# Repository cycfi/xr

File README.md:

# xr
XR Extended Response Pickups

The Cycfi XR Extended Response Pickups utilize low-impedance coils (Lo-Z 350Ω to 500Ω DCR) which 
inherently have full frequency response from 20Hz to 20kHz and beyond. Unlike traditional high-
impedance passive pickups there are no big peaks and dips in the spectrum, typically perceived as 
the pickup’s “character”. That does not mean that Lo-Z pickups lack character. In fact a Lo-Z coil’s 
characteristically wide bandwidth gives it a voice all its own. The pickups are very rich in harmonics, 
with uber-clean sounds, lots of overtones and crystal clear highs. They have a lot more harmonic 
content than even the bright Stratocaster pickup (which has frequency response that rolls off at 
around 5KHz.) On the low end of the audio spectrum you get tight, well-defined and focused bass 
all the way down to 20Hz.

This work is licensed under a [Creative Commons Attribution-NonCommercial 4.0 
International License](http://creativecommons.org/licenses/by-nc/4.0/).

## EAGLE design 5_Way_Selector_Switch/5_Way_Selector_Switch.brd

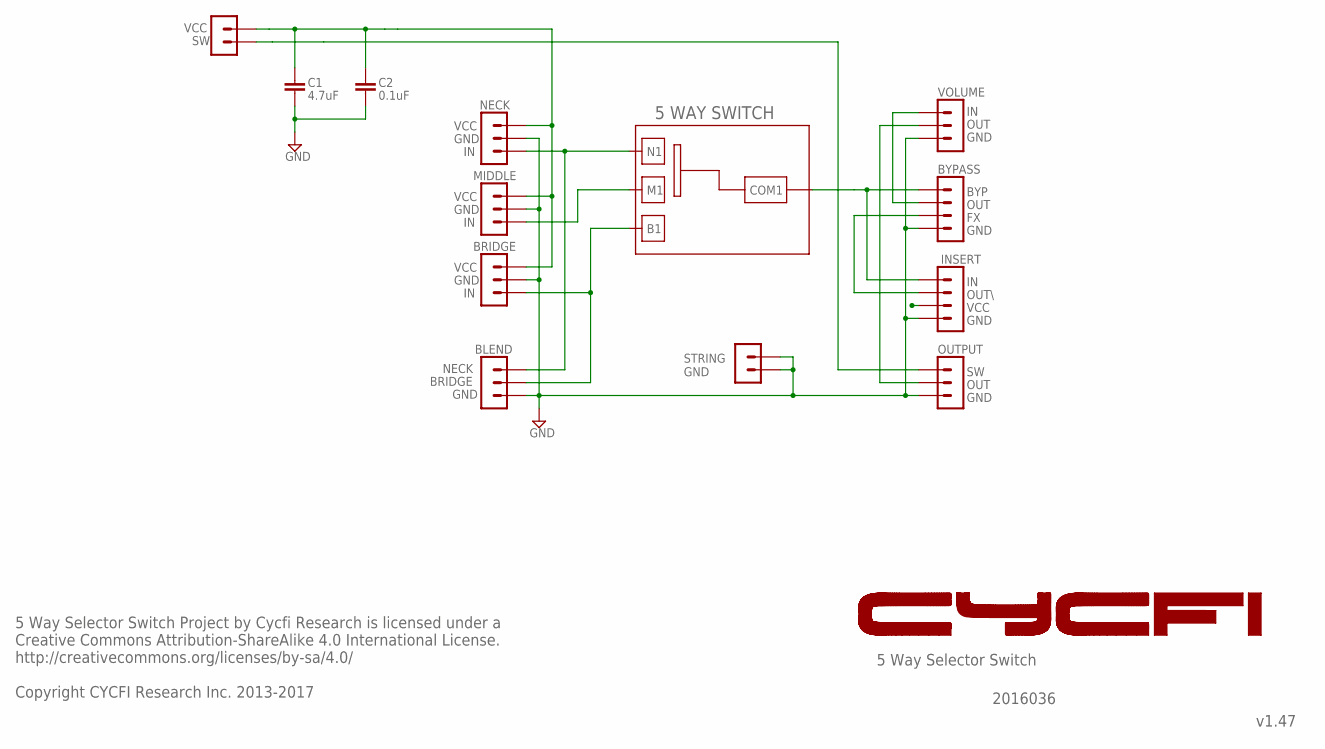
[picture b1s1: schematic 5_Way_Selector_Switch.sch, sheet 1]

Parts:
C1: 4.7uF; C0603
C2: 0.1uF; C0603
H3: 2PIN-SMD-2.54MM; 2P-SMD-2.54MM
U$3: 5WAY_SW_1; 5WAY_SW_CASTELLATED

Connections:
5WOUT: U$3.COM1; also elsewhere on the board
9V: C1.1, C2.1; also elsewhere on the board
B1: U$3.B1; also elsewhere on the board
GND: C1.2, C2.2, H3.P$1 (1), H3.P$2 (2); also elsewhere on the board
M1: U$3.M1; also elsewhere on the board
N1: U$3.N1; also elsewhere on the board

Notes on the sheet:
STRING GND
VCC
GND
NECK
BRIDGE
BLEND
BYP
OUT
OUT\
VOLUME
INSERT
OUTPUT
BYPASS
5 Way Selector Switch
v1.47
5 Way Selector Switch Project by Cycfi Research is licensed under a Creative Commons Attribution-ShareAlike 4.0 International License. http://creativecommons.org/licenses/by-sa/4.0/ Copyright CYCFI Research Inc. 2013-2017
2016036
MIDDLE

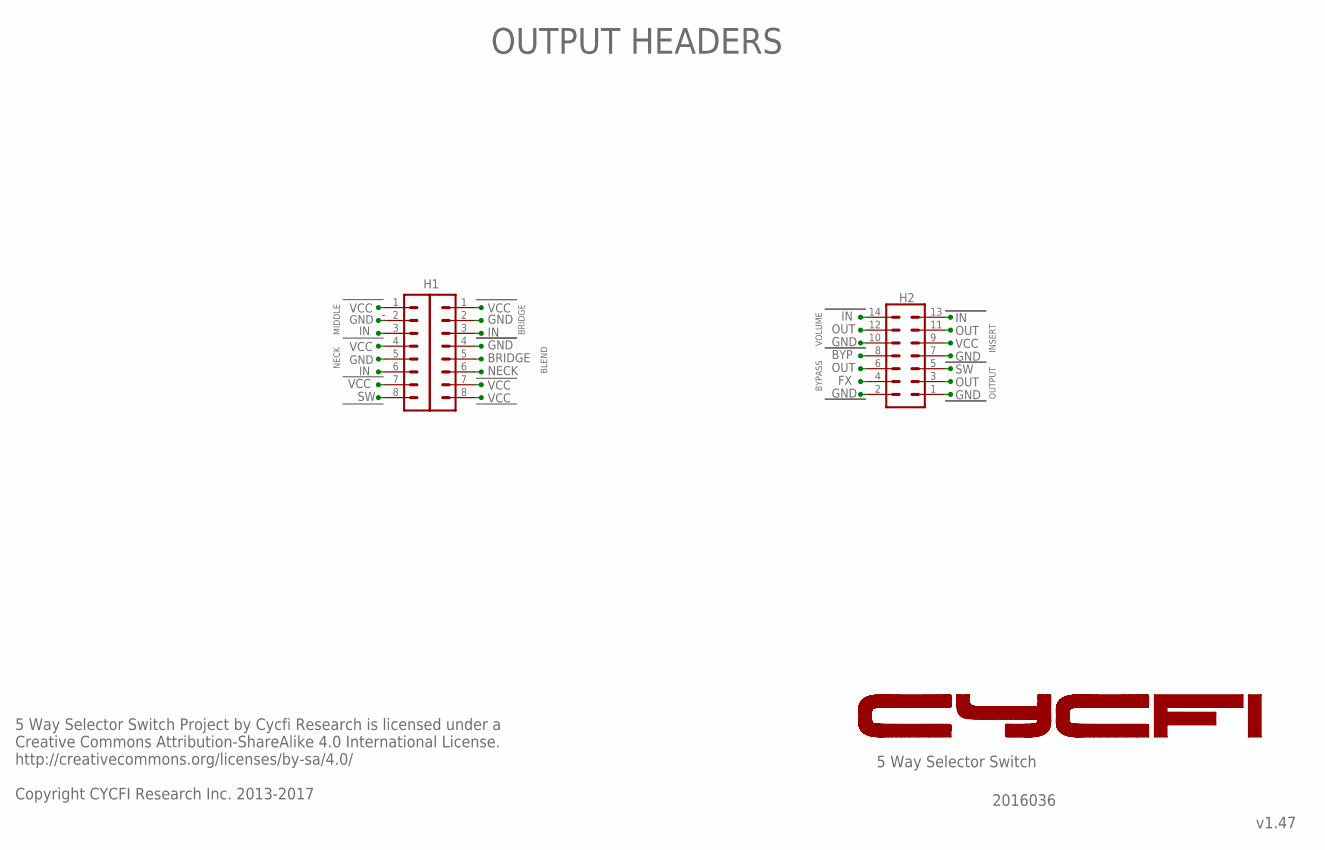
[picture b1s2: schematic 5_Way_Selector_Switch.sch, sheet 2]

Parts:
H2: MA07-2
SV1, SV2: MA08-1_

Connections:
5WOUT: H2.8, H2.13; also elsewhere on the board
9V: H2.9, SV1.1, SV1.7, SV1.8, SV2.1, SV2.4, SV2.7; also elsewhere on the board
B1: SV1.3, SV1.5; also elsewhere on the board
FX: H2.4, H2.11
GND: H2.1, H2.2, H2.7, H2.10, SV1.2, SV1.4, SV2.2, SV2.5; also elsewhere on the board
IN_VOL/MAIN_OUT: H2.6, H2.14
M1: SV2.3; also elsewhere on the board
N1: SV1.6, SV2.6; also elsewhere on the board
OUT(VOL): H2.3, H2.12
SW: H2.5, SV2.8

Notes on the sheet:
BYP
OUT
GND
VCC
NECK
BRIDGE
VOLUME
BYPASS
INSERT
OUTPUT
5 Way Selector Switch
v1.47
5 Way Selector Switch Project by Cycfi Research is licensed under a Creative Commons Attribution-ShareAlike 4.0 International License. http://creativecommons.org/licenses/by-sa/4.0/ Copyright CYCFI Research Inc. 2013-2017
2016036
OUTPUT HEADERS
BLEND
MIDDLE

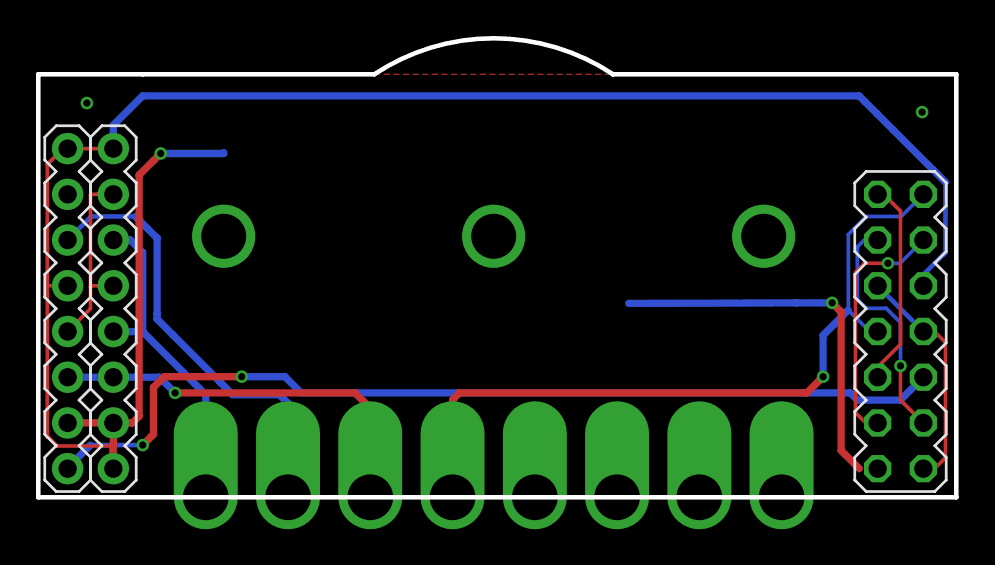
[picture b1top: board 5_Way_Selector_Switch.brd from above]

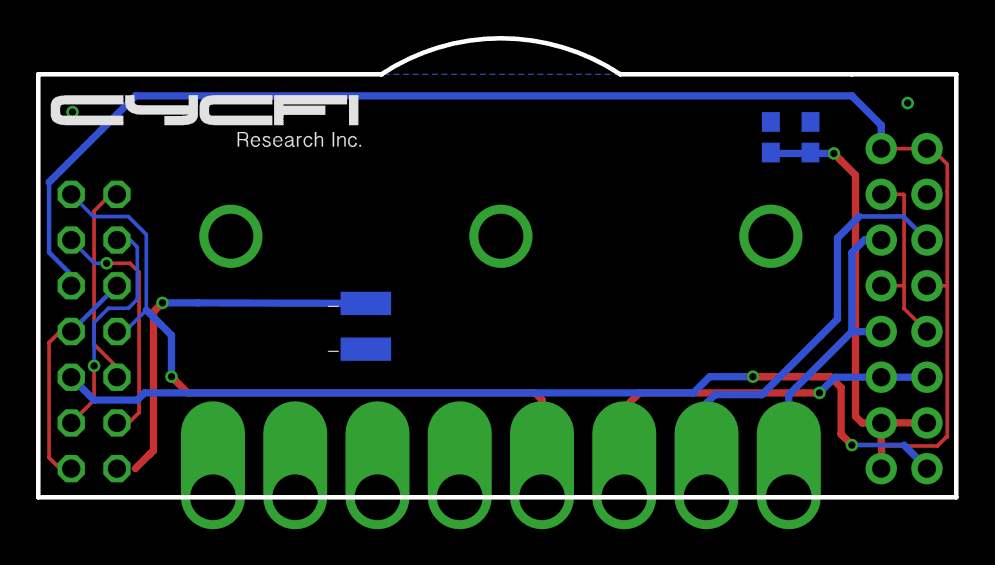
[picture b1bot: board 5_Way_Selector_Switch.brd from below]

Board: 2 copper layers, 51.0 x 25.5 mm, 7 parts (3 on the bottom side), 10 nets.

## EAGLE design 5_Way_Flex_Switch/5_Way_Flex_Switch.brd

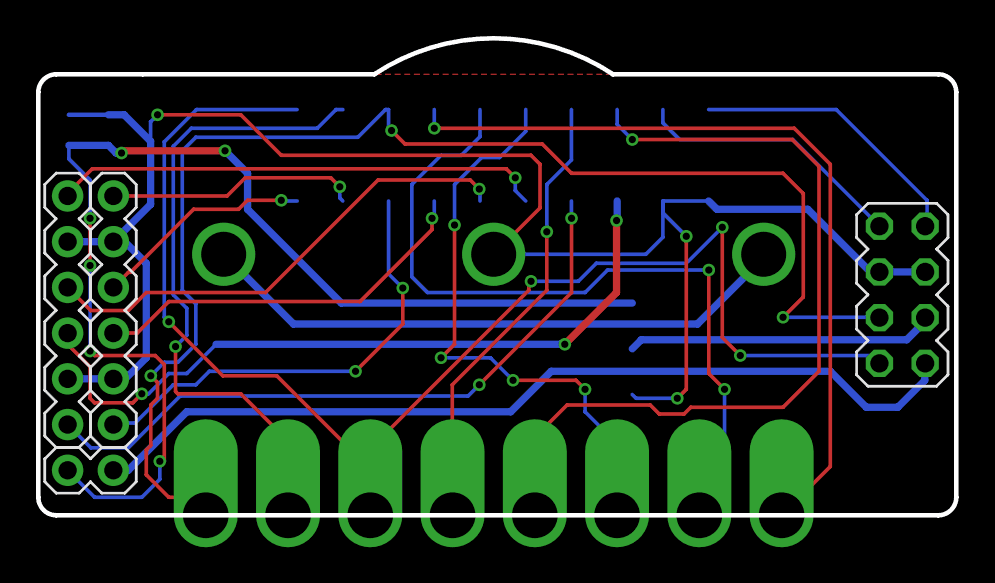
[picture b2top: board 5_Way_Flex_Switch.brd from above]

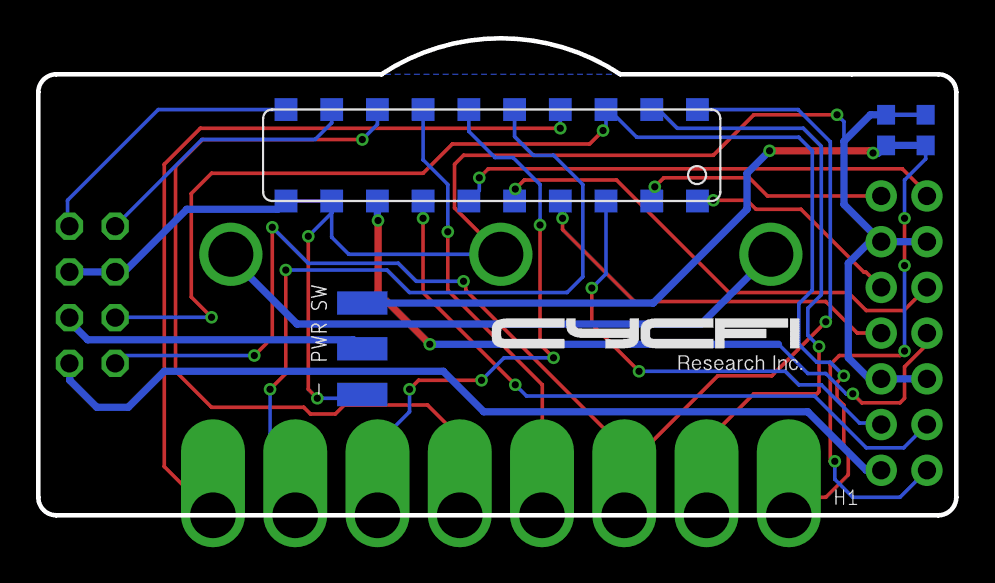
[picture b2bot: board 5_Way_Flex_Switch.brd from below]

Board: 2 copper layers, 51.0 x 26.5 mm, 9 parts (3 on the bottom side), 22 nets.

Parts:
C1: 4.7uF; C0603
C2: 0.1uF; C0603
CB1: CONFIGURATION_BRD_PADS
H1: MA02-1
H2: MA04-2
H3: 3PIN-SMD-2.54MM; 3P-SMD-2.54MM
H4, H5: MA06-1_
U$1: 5WAY_SW_CASTELLATED

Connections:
1-IC: CB1.1-IC, H4.3
1-OC: CB1.1-OC, H4.1
2-IC: CB1.2-IC, H4.6
2-OC: CB1.2-OC, H4.4
3-IC: CB1.3-IC, H5.3
3-OC: CB1.3-OC, H5.1
4-IC: CB1.4-IC, H5.6
4-OC: CB1.4-OC, H5.4
B1: CB1.B1, H2.4, U$1.B1
GND: C1.2, C2.2, CB1.GND, CB1.GND1, H2.5, H2.6, H3.P$3, H4.2, H4.5, H5.2, H5.5
IN+: CB1.OUT-, H2.7
IN-: CB1.OUT+, H2.8
N1: CB1.N1, H2.2, U$1.N1
unnamed: CB1.COM2, U$1.COM2
unnamed: CB1.COM1, U$1.COM1
unnamed: CB1.M1, U$1.M1
unnamed: CB1.N2, U$1.N2
unnamed: CB1.M2, U$1.M2
unnamed: CB1.B2, U$1.B2
SW: H1.1, H2.1
VBATT: C1.1, C2.1, H1.2, H3.P$1
VCC: H2.3, H3.P$2

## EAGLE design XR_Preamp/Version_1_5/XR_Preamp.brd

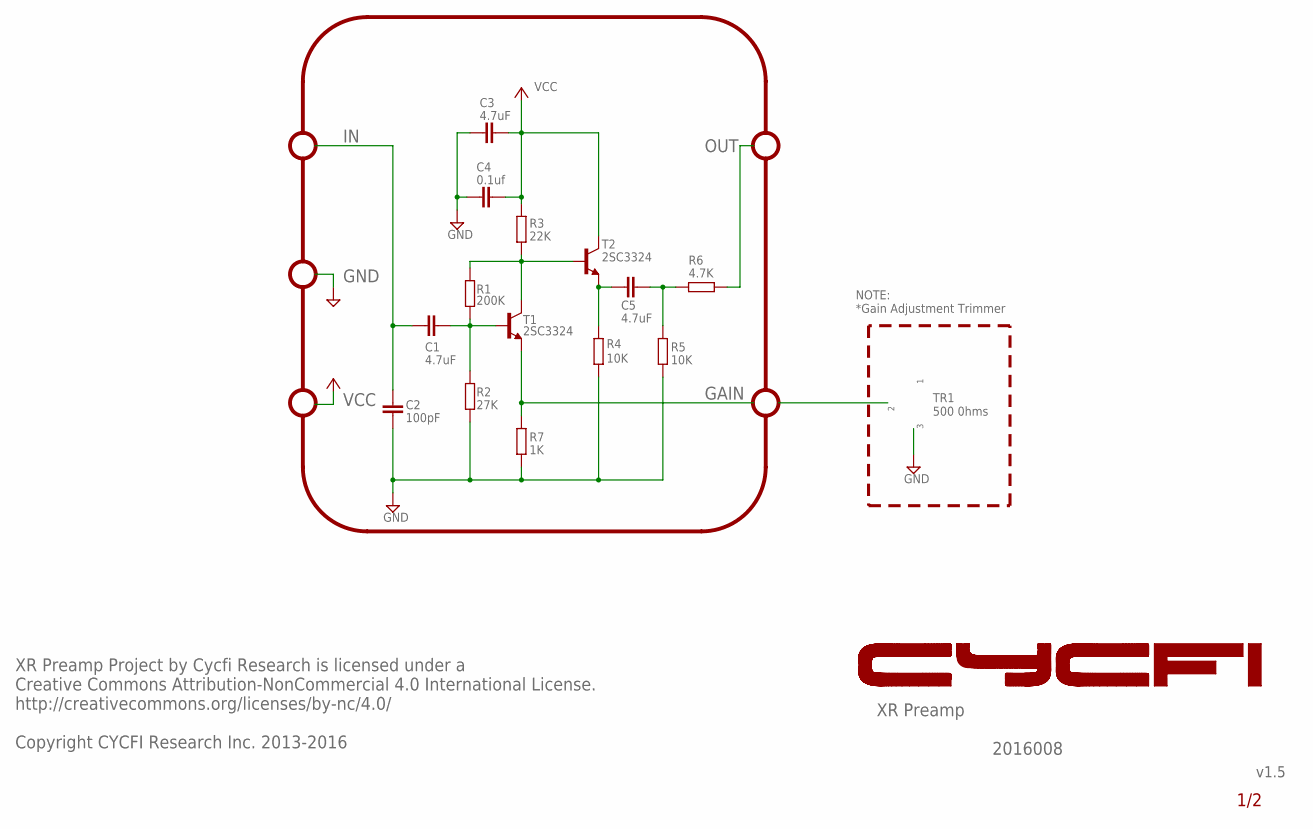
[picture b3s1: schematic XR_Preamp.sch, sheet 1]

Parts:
C1, C3: 4.7uF; C0603
C2: 100pF; C0402
C4: 0.1uf; C0402
C5: 4.7uF; C0402
R1: 200K; R0402
R2: 27K; R0402
R3: 22K; R0402
R4, R5: 10K; R0402
R6: 4.7K; R0402
R7: 1K; R0402
T1, T2: 2SC3324; SOT23

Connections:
GAIN: R7.2, T1.2 (E); also elsewhere on the board
GND: C2.1, C3.1, C4.1, R2.1, R4.1, R5.1, R7.1; also elsewhere on the board
IN: C1.1, C2.2; also elsewhere on the board
unnamed: C1.2, R1.1, R2.2, T1.1 (B)
unnamed: C5.2, R4.2, T2.2 (E)
OUT: R6.2; also elsewhere on the board
OUT1: C5.1, R5.2, R6.1
VCC: C3.2, C4.2, R3.2, T2.3 (C); also elsewhere on the board
VCVF: R1.2, R3.1, T1.3 (C), T2.1 (B)

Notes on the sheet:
TR1 500 0hms
NOTE: *Gain Adjustment Trimmer
XR Preamp
v1.5
XR Preamp Project by Cycfi Research is licensed under a Creative Commons Attribution-NonCommercial 4.0 International License. http://creativecommons.org/licenses/by-nc/4.0/ Copyright CYCFI Research Inc. 2013-2016
2016008
1/2

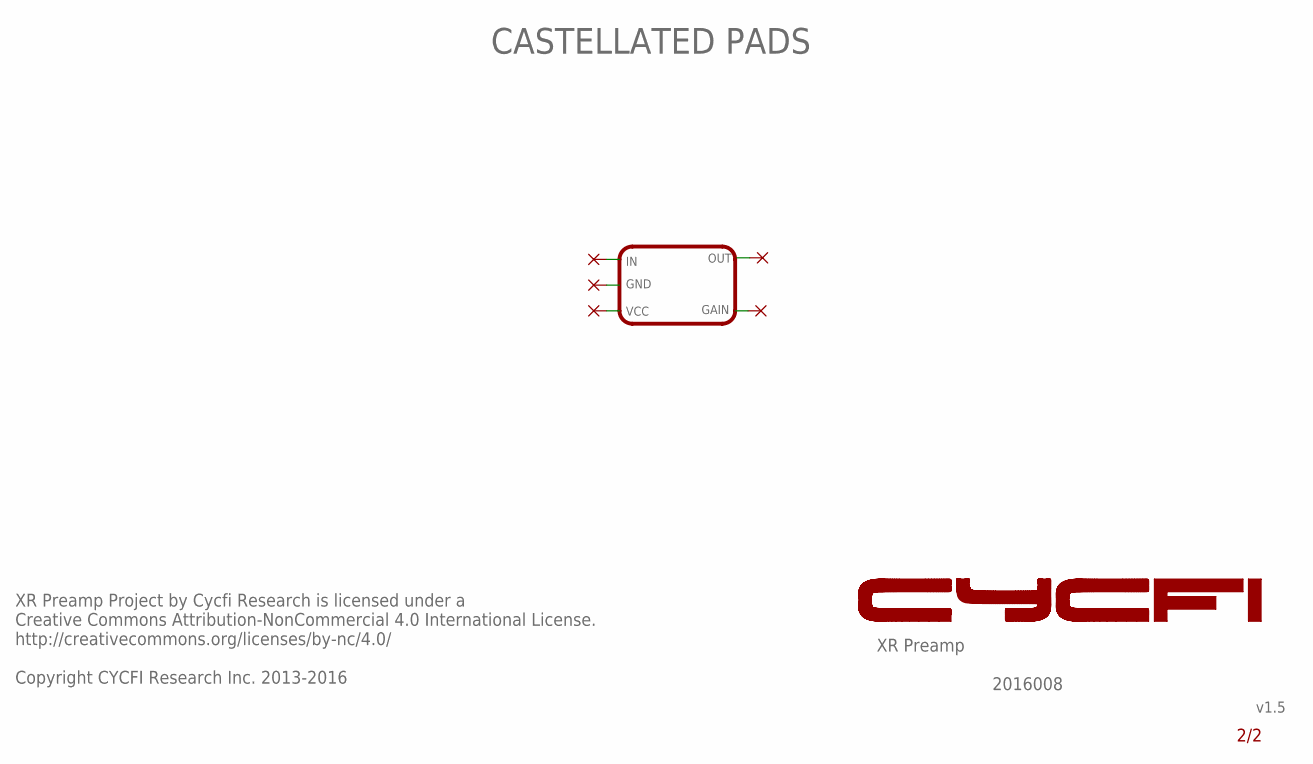
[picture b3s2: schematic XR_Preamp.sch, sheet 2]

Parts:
PAD1, PAD2, PAD3, PAD4, PAD5: WIREPAD2,15/1,0; 1,6/0,8

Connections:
GAIN: PAD1.1; also elsewhere on the board
GND: PAD2.1; also elsewhere on the board
IN: PAD3.1; also elsewhere on the board
OUT: PAD5.1; also elsewhere on the board
VCC: PAD4.1; also elsewhere on the board

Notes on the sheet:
GND
VCC
CASTELLATED PADS
XR Preamp
v1.5
XR Preamp Project by Cycfi Research is licensed under a Creative Commons Attribution-NonCommercial 4.0 International License. http://creativecommons.org/licenses/by-nc/4.0/ Copyright CYCFI Research Inc. 2013-2016
2016008
2/2

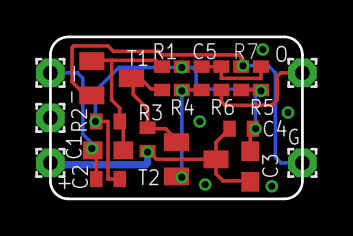
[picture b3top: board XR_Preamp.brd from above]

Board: 2 copper layers, 14.0 x 9.0 mm, 19 parts (0 on the bottom side), 9 nets.

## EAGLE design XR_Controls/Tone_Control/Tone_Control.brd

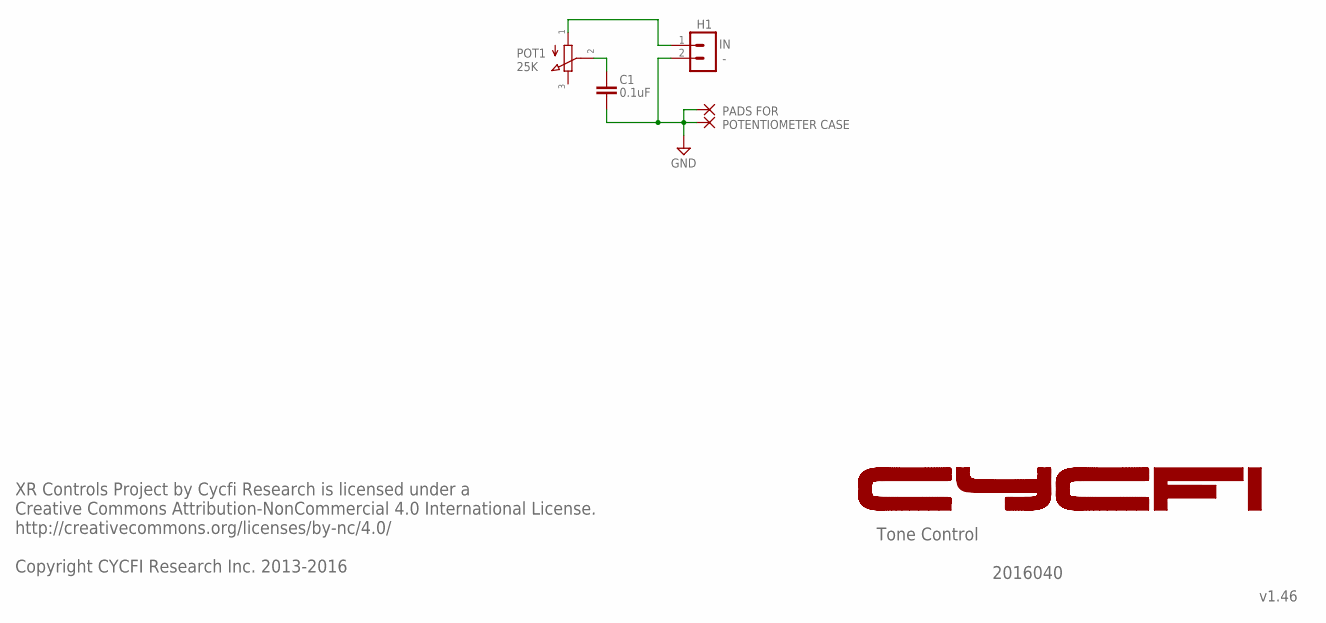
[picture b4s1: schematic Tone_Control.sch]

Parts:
C1: 0.1uF; C0603
GND3, GND4: SMD2; SMD1,27-2,54
H1: MA02-1
POT1: PDB181-GTR01; PDB181

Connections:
GND: C1.1, GND3.1, GND4.1, H1.2
unnamed: C1.2, POT1.P$2 (2)
unnamed: H1.1, POT1.P$1 (1)

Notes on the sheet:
PADS FOR POTENTIOMETER CASE
POT1 25K
Tone Control
v1.46
XR Controls Project by Cycfi Research is licensed under a Creative Commons Attribution-NonCommercial 4.0 International License. http://creativecommons.org/licenses/by-nc/4.0/ Copyright CYCFI Research Inc. 2013-2016
2016040

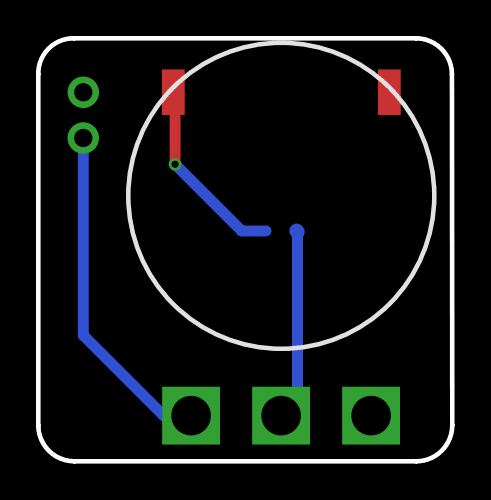
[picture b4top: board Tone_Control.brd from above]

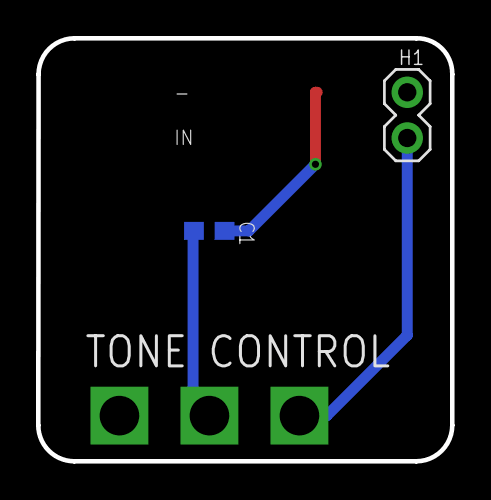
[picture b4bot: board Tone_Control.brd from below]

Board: 2 copper layers, 23.0 x 23.5 mm, 5 parts (2 on the bottom side), 3 nets.

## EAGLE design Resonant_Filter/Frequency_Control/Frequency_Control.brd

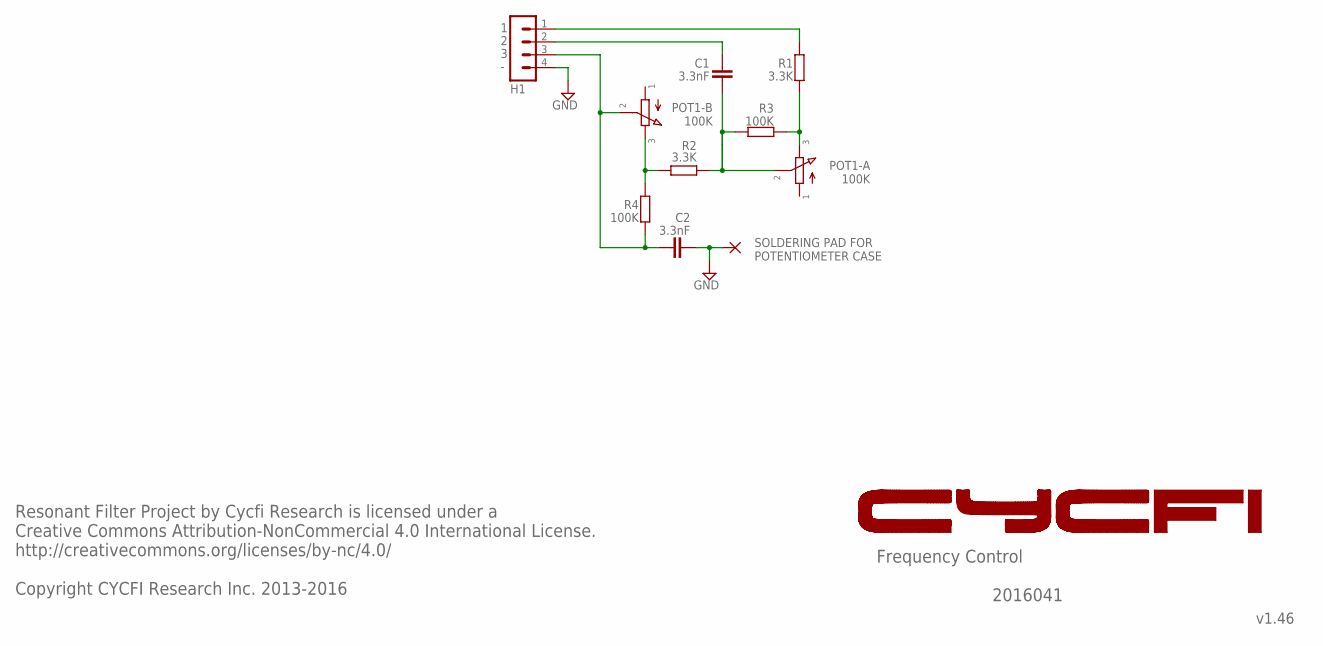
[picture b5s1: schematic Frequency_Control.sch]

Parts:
C1, C2: 3.3nF; C0805
H1: MA04-1
PAD1: 1,6/0,9
POT1-A: PDB182-GTR02; PDB182-GTR01
R1, R2: 3.3K; R0603
R3, R4: 100K; R0402

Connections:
1: H1.1, R1.1
2: C1.2, H1.2
3: C2.1, H1.3, POT1-A.B2 (2), R4.2
GND: C2.2, H1.4, PAD1.1
unnamed: POT1-A.A3 (3), R1.2, R3.2
unnamed: C1.1, POT1-A.A2 (2), R2.1, R3.1
unnamed: POT1-A.B3 (3), R2.2, R4.1

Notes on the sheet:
POT1-A 100K
POT1-B 100K
SOLDERING PAD FOR POTENTIOMETER CASE
Frequency Control
v1.46
Resonant Filter Project by Cycfi Research is licensed under a Creative Commons Attribution-NonCommercial 4.0 International License. http://creativecommons.org/licenses/by-nc/4.0/ Copyright CYCFI Research Inc. 2013-2016
2016041

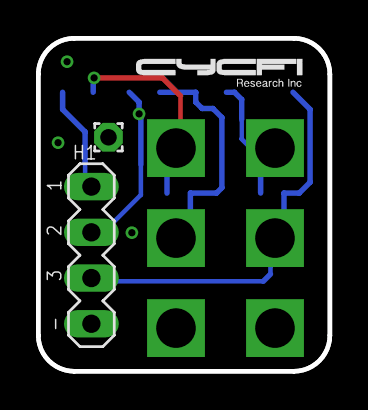
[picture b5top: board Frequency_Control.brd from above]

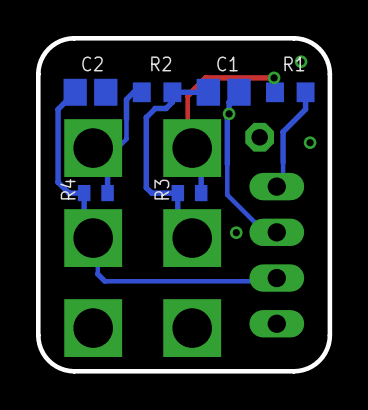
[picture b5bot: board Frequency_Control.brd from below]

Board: 2 copper layers, 16.2 x 18.5 mm, 9 parts (6 on the bottom side), 7 nets.

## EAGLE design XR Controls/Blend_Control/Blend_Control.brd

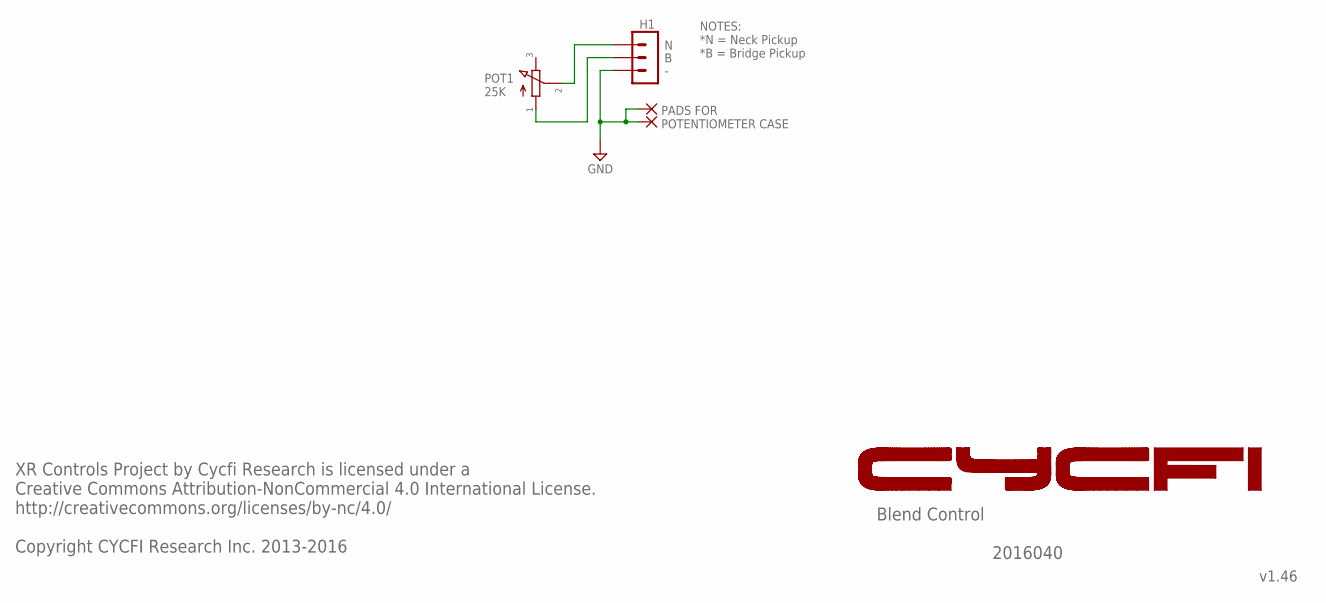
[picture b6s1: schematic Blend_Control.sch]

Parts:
GND3, GND4: SMD2; SMD1,27-2,54
H1: 3PIN-SMD-2.54MM; 3P-SMD-2.54MM
POT1: PDB181-GTR01; PDB181

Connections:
GND: GND3.1, GND4.1, H1.P$1 (1)
unnamed: H1.P$3 (3), POT1.P$2 (2)
unnamed: H1.P$2 (2), POT1.P$1 (1)

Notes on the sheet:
PADS FOR POTENTIOMETER CASE
NOTES: *N = Neck Pickup *B = Bridge Pickup
POT1 25K
Blend Control
v1.46
XR Controls Project by Cycfi Research is licensed under a Creative Commons Attribution-NonCommercial 4.0 International License. http://creativecommons.org/licenses/by-nc/4.0/ Copyright CYCFI Research Inc. 2013-2016
2016040

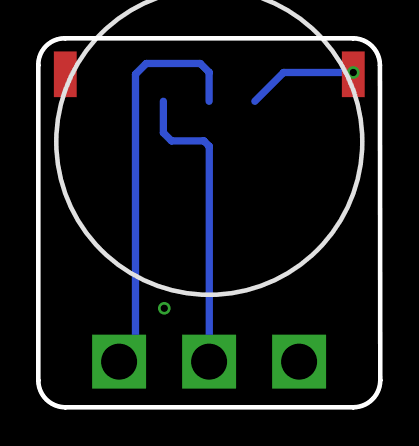
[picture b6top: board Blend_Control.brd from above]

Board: 2 copper layers, 19.0 x 20.5 mm, 4 parts (1 on the bottom side), 3 nets.

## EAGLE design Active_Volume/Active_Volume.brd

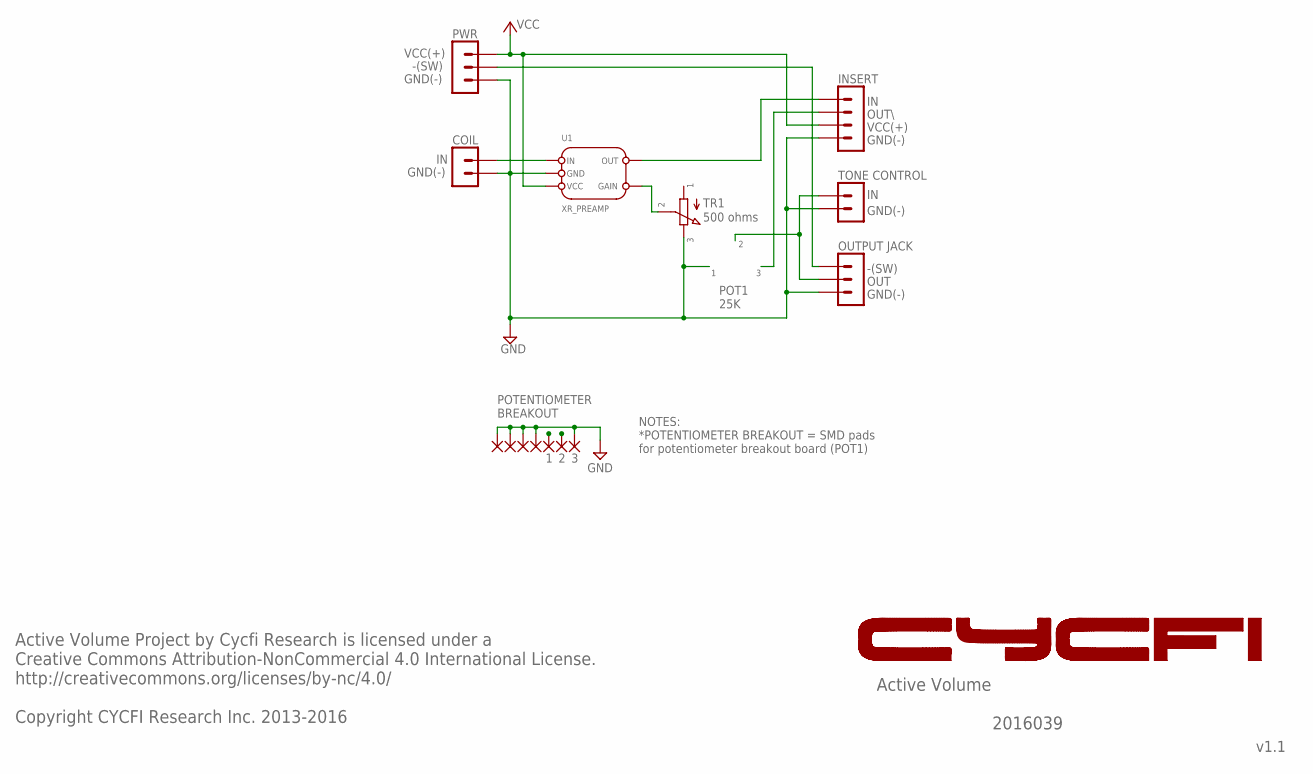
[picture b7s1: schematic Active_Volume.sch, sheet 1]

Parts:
PAD1, PAD2, PAD3, PAD4, PAD5, PAD6, PAD7: SMD2; SMD1,27-2,54
TR1: TC33X-2-201E
U1: XR_PREAMP; XR_PREAMP_V1.5

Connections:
GND: PAD1.1, PAD4.1, PAD5.1, PAD6.1, PAD7.1, TR1.P$3 (3), U1.GND; also elsewhere on the board
INPUT: U1.IN; also elsewhere on the board
unnamed: TR1.P$2 (2), U1.GAIN
OUT(PREAMP): U1.OUT; also elsewhere on the board
OUT(SEL): PAD2.1; also elsewhere on the board
OUT(VOL): PAD3.1; also elsewhere on the board
VCC: U1.VCC; also elsewhere on the board

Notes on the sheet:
POTENTIOMETER BREAKOUT
POT1 25K
-(SW)
VCC(+)
GND(-)
OUT\
OUT
PWR
INSERT
OUTPUT JACK
COIL
TONE CONTROL
500 ohms
NOTES: *POTENTIOMETER BREAKOUT = SMD pads for potentiometer breakout board (POT1)
Active Volume
v1.1
Active Volume Project by Cycfi Research is licensed under a Creative Commons Attribution-NonCommercial 4.0 International License. http://creativecommons.org/licenses/by-nc/4.0/ Copyright CYCFI Research Inc. 2013-2016
2016039

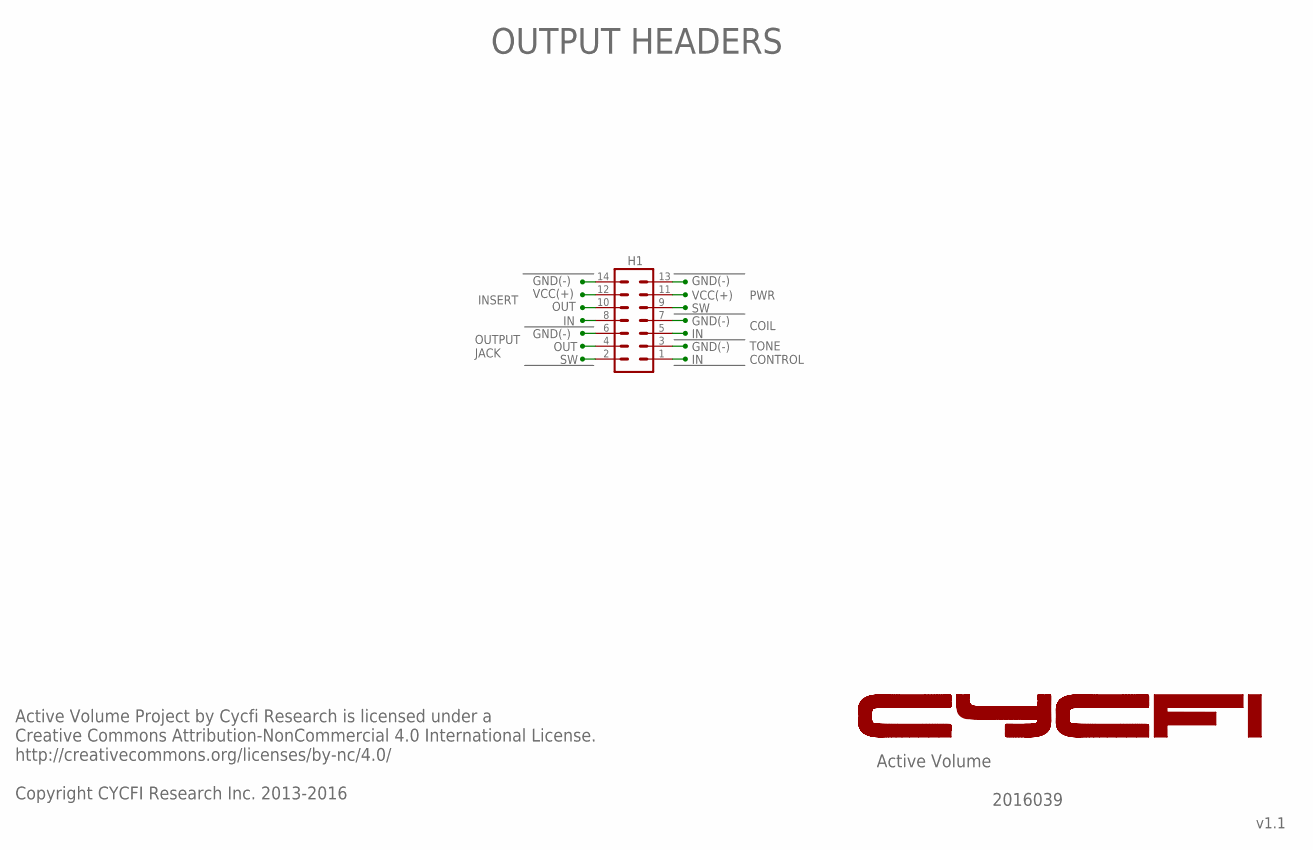
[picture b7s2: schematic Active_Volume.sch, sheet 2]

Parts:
H1: MA07-2

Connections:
GND: H1.3, H1.6, H1.7, H1.13, H1.14; also elsewhere on the board
INPUT: H1.5; also elsewhere on the board
OUT(PREAMP): H1.8; also elsewhere on the board
OUT(SEL): H1.10; also elsewhere on the board
OUT(VOL): H1.1, H1.4; also elsewhere on the board
SW: H1.2, H1.9
VCC: H1.11, H1.12; also elsewhere on the board

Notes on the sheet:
OUT
Active Volume
v1.1
Active Volume Project by Cycfi Research is licensed under a Creative Commons Attribution-NonCommercial 4.0 International License. http://creativecommons.org/licenses/by-nc/4.0/ Copyright CYCFI Research Inc. 2013-2016
2016039
GND(-)
VCC(+)
OUTPUT HEADERS
INSERT
OUTPUT JACK
PWR
TONE CONTROL
COIL

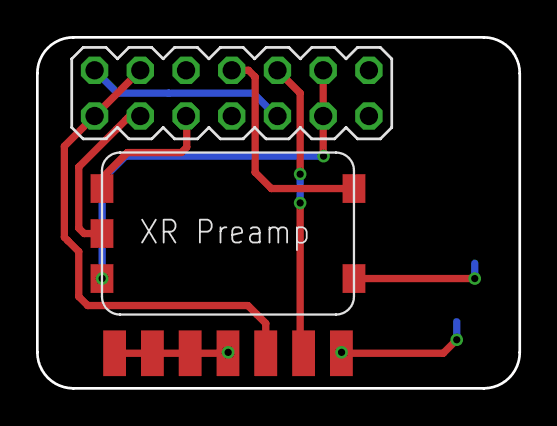
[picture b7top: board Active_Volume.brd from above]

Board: 2 copper layers, 26.8 x 19.5 mm, 10 parts (1 on the bottom side), 8 nets.

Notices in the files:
XR_Controls/Blend_Control/Blend_Control.sch:
Blend Control Project by Cycfi Research is licensed under a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
XR_Preamp/XR_Preamp.sch:
XR Preamp for XR Project by Cycfi Research is licensed under a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
